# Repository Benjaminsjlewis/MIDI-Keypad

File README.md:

# MIDI-Keypad
And then your actual MIDI keys will use capacitive touch which just uses exposed copper on the PCB which uses the electrical field from your body to detect presses!
We'll be using these core components, and you should use any amount and combination of them for your design:

EC11 Rotary Encoders
SK6812 MINI-E Neopixels
Bourns Slide Potentiometers
Kailh Choc Low-Profile Switches

KiCad has tens of thousands of parts for you to use in the editor, but they're still missing a couple which we'll need to install. 

I make it very cute!!!

Make it look like a piano 

        Designator        Footprint                                             Quantity              Value                              Total Cost          Part
        
        D1, D2, D3        LED_SK6812MINI-E_3.2x2.8mm_P1.5mm_ReverseMount            3              SK6812MINI-E                              $3.36	    https://www.aliexpress.us/item/3256807677321116.html?
        J1                Capacitive Keys                                           1              Capacitive Touch Buttons                  $3.33          https://www.amazon.com/MPR121-Capacitive-Buttons-Sensitive-
        RV1, RV2          Potentiometer_Bourns_PTA1543_Single_Slide	            2              Slider                                    $3.16          https://www.digikey.com/en/products/detail/bourns-inc/PTA1543-2010CIB103/3781161
       SW1, SW2, SW3     Kailh Choc Low-Profile Switches                            3              SW_Push                                   $6.04          https://www.aliexpress.com/item/1005008883418065.html?
       SW4               RotaryEncoder_Alps_EC11E-Switch_Vertical_H20mm	            1              RotaryEncoder_Switch_MP                   $1.44          https://www.aliexpress.us/item/3256807457768762.html?
        U1                Waveshare ESP32-S3-Zero                                   1              Waveshare ESP32-S3-ZERO                   $6.62          https://www.aliexpress.com/item/1005007004089798.html?src=google&gatewayAdapt=4itemAdapt

                                                                                                    Total Aliexpress:                         $19.59	   
                                                                                                    Total Digikey:	                       $12.35	
                                                                                                    Total JLCPCB:	                          $12.29	
                                                                                                    Total:                                  	$44.23

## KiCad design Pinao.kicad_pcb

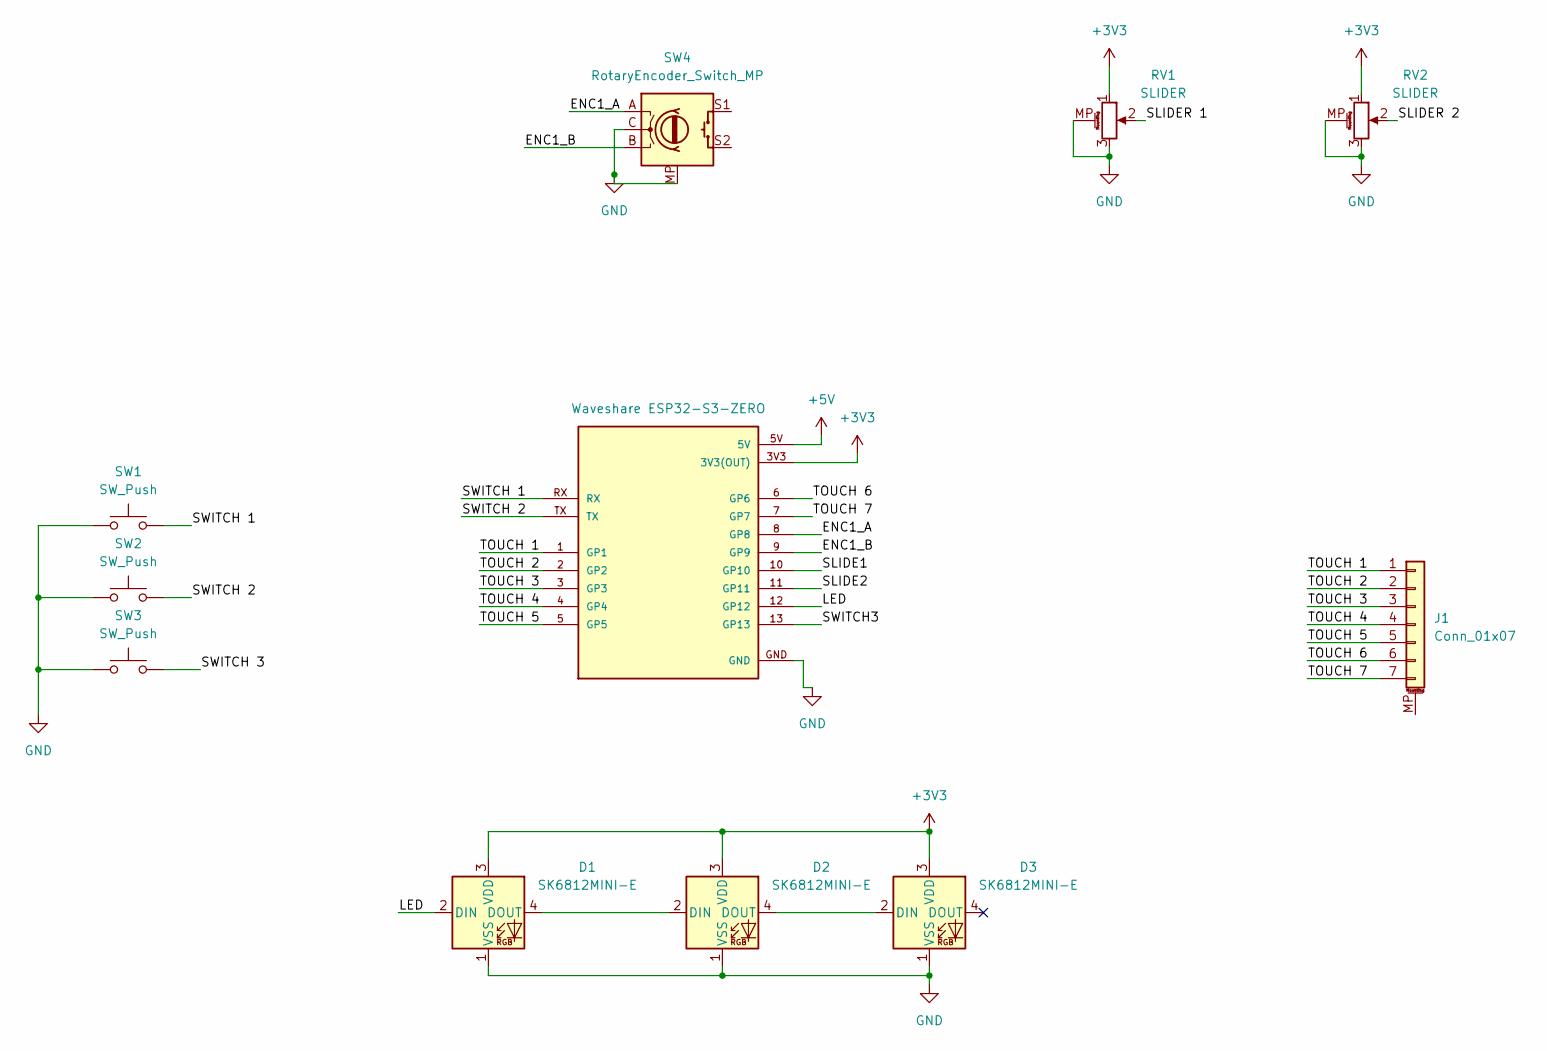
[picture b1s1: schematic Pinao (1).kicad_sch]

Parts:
D1, D2, D3: SK6812MINI-E; LED_SK6812MINI-E_3.2x2.8mm_P1.5mm_ReverseMount
J1: Conn_01x07; Piano Keys TEST RIGHT BEST ONE
RV1, RV2: SLIDER; Potentiometer_Bourns_PTA1543_Single_Slide
SW1, SW2, SW3: SW_Push; Kailh Choc Low-Profile Switches
SW4: RotaryEncoder_Switch_MP; RotaryEncoder_Alps_EC11E_Vertical_H20mm
U1: Waveshare ESP32-S3-ZERO; Waveshare ESP32-S3-Zero; PARTREV NA

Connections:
+3V3: D1.3 (VDD), D2.3 (VDD), D3.3 (VDD), RV1.1, RV2.1, U1.3V3 (3V3(OUT))
+5V: U1.5V
/ENC1_A: SW4.A, U1.8 (GP8)
/ENC1_B: SW4.B, U1.9 (GP9)
/LED: D1.2 (DIN), U1.12 (GP12)
/SLIDE1: U1.10 (GP10)
/SLIDE2: U1.11 (GP11)
/SLIDER 1: RV1.2
/SLIDER 2: RV2.2
/SWITCH3: U1.13 (GP13)
/SWITCH 1: SW1.2, U1.RX
/SWITCH 2: SW2.2, U1.TX
/SWITCH 3: SW3.2
/TOUCH 1: J1.1, U1.1 (GP1)
/TOUCH 2: J1.2, U1.2 (GP2)
/TOUCH 3: J1.3, U1.3 (GP3)
/TOUCH 4: J1.4, U1.4 (GP4)
/TOUCH 5: J1.5, U1.5 (GP5)
/TOUCH 6: J1.6, U1.6 (GP6)
/TOUCH 7: J1.7, U1.7 (GP7)
GND: D1.1 (VSS), D2.1 (VSS), D3.1 (VSS), RV1.3, RV1.MP (MountPin), RV2.3, RV2.MP (MountPin), SW1.1, SW2.1, SW3.1, SW4.C, SW4.MP, U1.GND
unnamed: D1.4 (DOUT), D2.2 (DIN)
unnamed: D2.4 (DOUT), D3.2 (DIN)

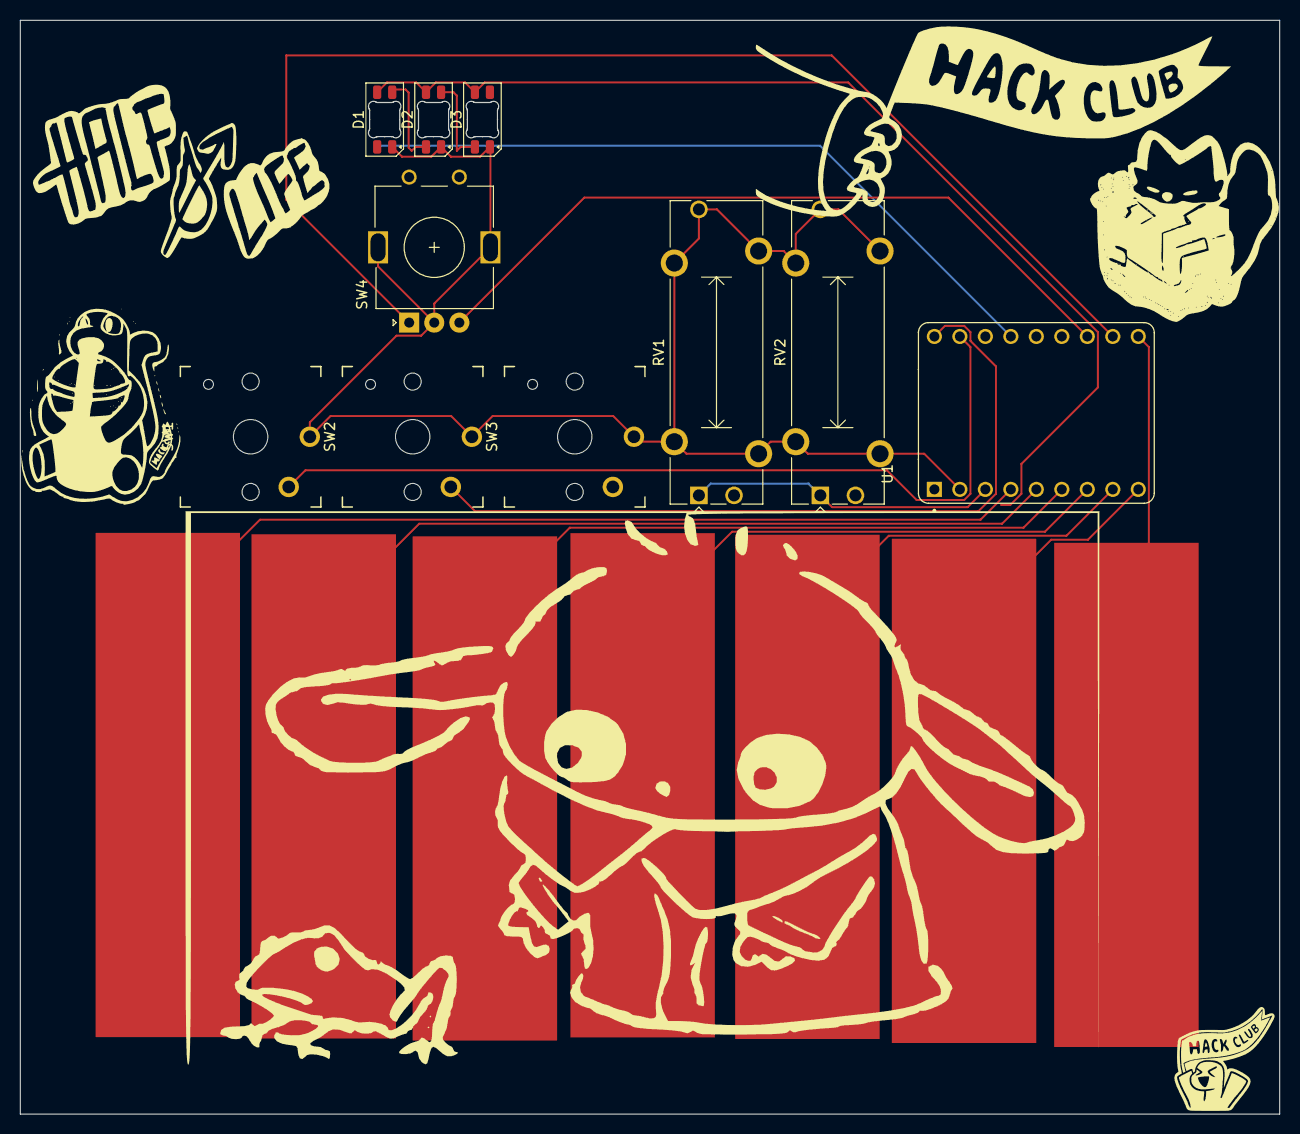
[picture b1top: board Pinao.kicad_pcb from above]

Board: 2 copper layers, 125.5 x 109.0 mm, 11 parts (0 on the bottom side), 16 nets.

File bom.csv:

Designator        Footprint                                             Quantity              Value                              Total Cost          Part
D1, D2, D3        LED_SK6812MINI-E_3.2x2.8mm_P1.5mm_ReverseMount            3              SK6812MINI-E                             $3.36	            https://www.aliexpress.us/item/3256807677321116.html?
J1                Capacitive Keys                                           1              Capacitive Touch Buttons
RV1, RV2          Potentiometer_Bourns_PTA1543_Single_Slide	                2              Slider                                    $3.16            https://www.digikey.com/en/products/detail/bourns-inc/PTA154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
SW1, SW2, SW3     Kailh Choc Low-Profile Switches                           3              SW_Push                                    $6.04          https://www.aliexpress.com/item/1005008883418065.html?
SW4               RotaryEncoder_Alps_EC11E-Switch_Vertical_H20mm	          1              RotaryEncoder_Switch_MP                    $1.44          https://www.aliexpress.us/item/3256807457768762.html?
U1                Waveshare ESP32-S3-Zero                                   1              Waveshare ESP32-S3-ZERO                    $6.62          https://www.aliexpress.com/item/1005007004089798.html?src=go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

                                                                                            Total Aliexpress:                         $19.59	   
                                                                                            Total Digikey:	                          $12.35	
                                                                                            Total JLCPCB:	                            $12.29	
                                                                                            Total:                                  	$44.23
